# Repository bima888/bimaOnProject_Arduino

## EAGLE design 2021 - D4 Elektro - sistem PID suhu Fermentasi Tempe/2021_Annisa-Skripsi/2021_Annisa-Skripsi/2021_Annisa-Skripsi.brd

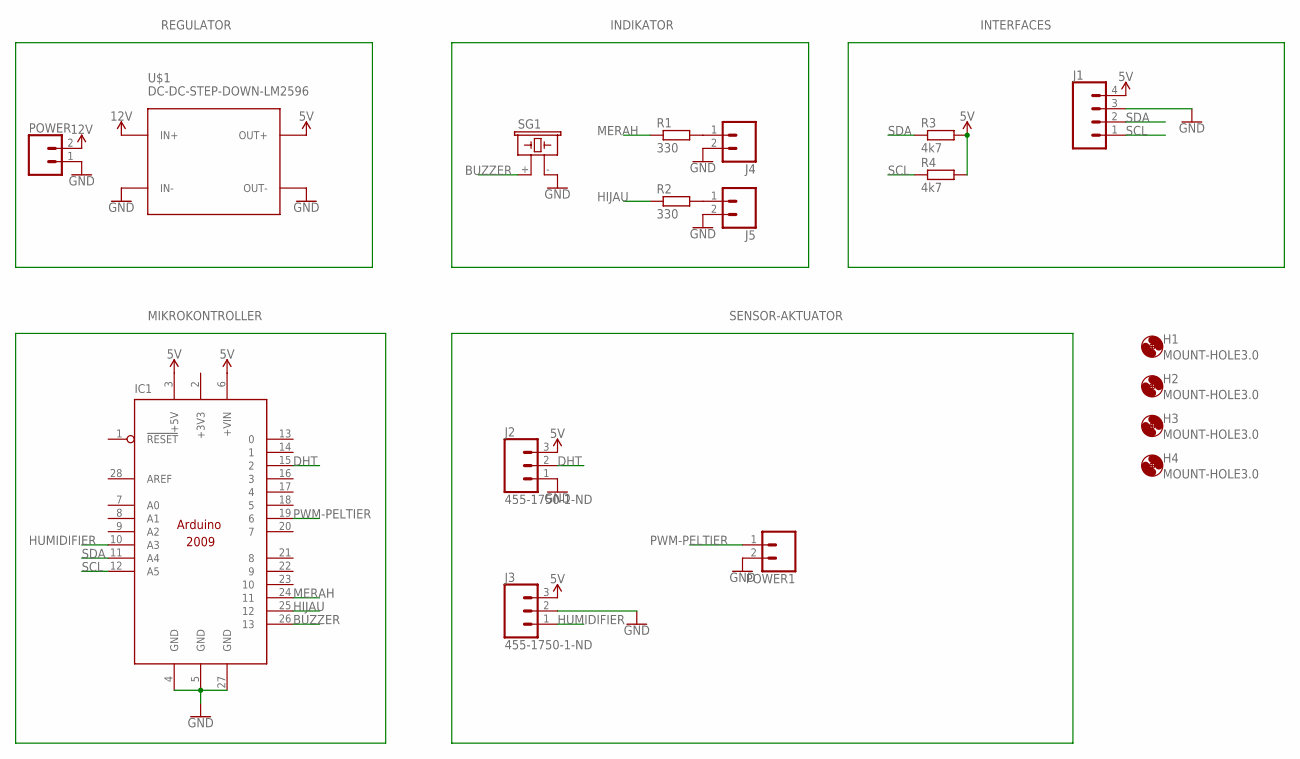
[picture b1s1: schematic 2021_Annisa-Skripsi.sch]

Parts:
H1, H2, H3, H4: MOUNT-HOLE3.0; 3,0
IC1: ARDUINO2009_10; ARDUINO2009
J1: CONN_04PTH; 1X04
J2, J3: 455-1750-1-ND; 1X03
J4, J5: CONN_02; 1X02
POWER, POWER1: CONN_025MM; SCREWTERMINAL-5MM-2
R1, R2: 330; 0207/7
R3, R4: 4k7; 0207/7
SG1: F/CM12P
U$1: DC-DC-STEP-DOWN-LM2596

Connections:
5V: IC1.3 (+5V), IC1.6 (+VIN), J1.4, J2.3, J3.3, R3.2, R4.2, U$1.OUT+
12V: POWER.2, U$1.IN+
+3V3: IC1.2 (+3V3)
BUZZER: IC1.26 (13), SG1.+ (1)
DHT: IC1.15 (2), J2.2
GND: IC1.4 (GND), IC1.5 (GND), IC1.27 (GND), J1.3, J2.1, J3.2, J4.2, J5.2, POWER.1, POWER1.2, SG1.- (2), U$1.IN-, U$1.OUT-
HIJAU: IC1.25 (12), R2.1
HUMIDIFIER: IC1.10 (A3), J3.1
MERAH: IC1.24 (11), R1.1
unnamed: J4.1, R1.2
unnamed: J5.1, R2.2
PWM-PELTIER: IC1.19 (6), POWER1.1
SCL: IC1.12 (A5), J1.1, R4.1
SDA: IC1.11 (A4), J1.2, R3.1

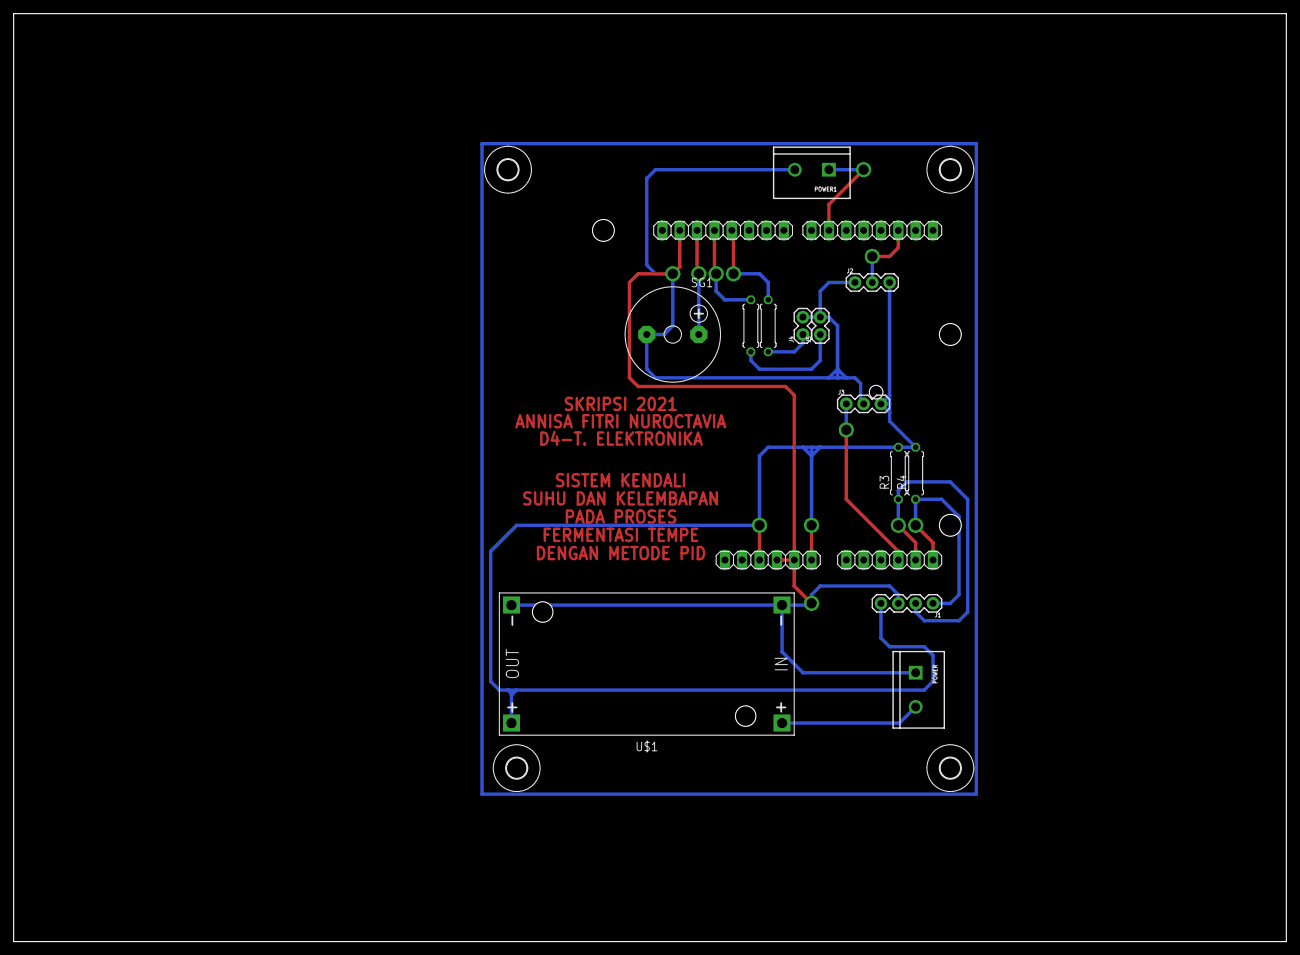
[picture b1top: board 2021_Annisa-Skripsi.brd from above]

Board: 2 copper layers, 186.4 x 135.9 mm, 18 parts (0 on the bottom side), 13 nets.

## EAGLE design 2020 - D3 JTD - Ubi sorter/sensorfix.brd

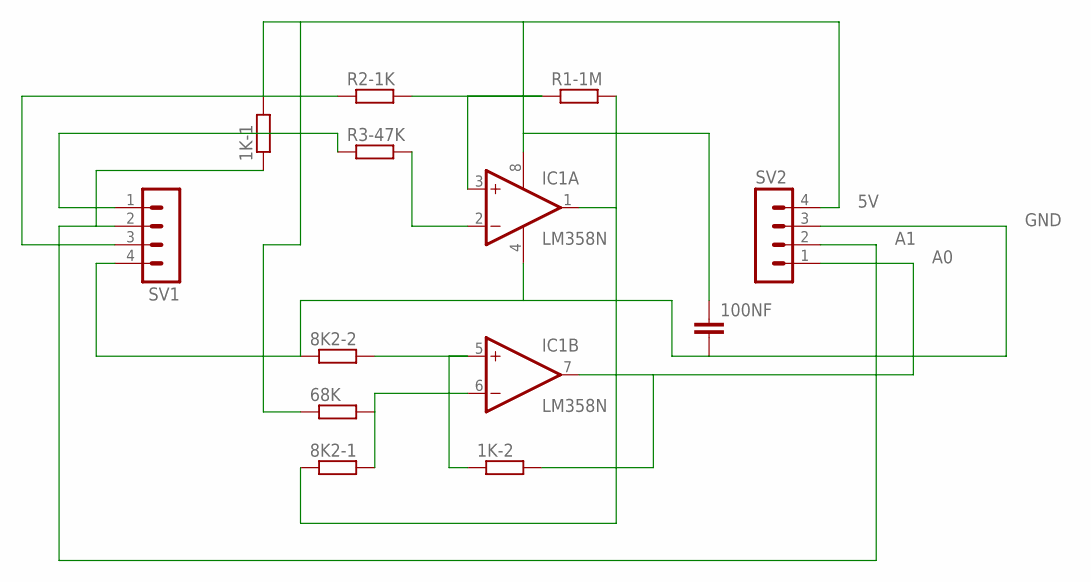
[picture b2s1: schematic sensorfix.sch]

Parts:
1K-1, 1K-2, 8K2-1, 8K2-2, 68K: R-EU_0309/12; 0309/12
100NF: C2.5/6; C2.5-6
IC1: LM358N; DIL08
R1-1M, R2-1K, R3-47K: R-EU_0309/12; 0309/12
SV1, SV2: MA04-1

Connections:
5V: 1K-1.2, 68K.1, 100NF.1, IC1.8 (V+), SV2.4
A0: 1K-2.2, IC1.7 (OUT), SV2.1
A1: 1K-1.1, SV1.2, SV2.2
GND: 8K2-2.1, 100NF.2, IC1.4 (V-), SV1.4, SV2.3
unnamed: IC1.3 (+IN), R1-1M.1, R2-1K.2
unnamed: 8K2-1.1, IC1.1 (OUT), R1-1M.2
unnamed: IC1.2 (-IN), R3-47K.2
unnamed: 1K-2.1, 8K2-2.2, IC1.5 (+IN)
unnamed: 8K2-1.2, 68K.2, IC1.6 (-IN)
unnamed: R3-47K.1, SV1.1
unnamed: R2-1K.1, SV1.3

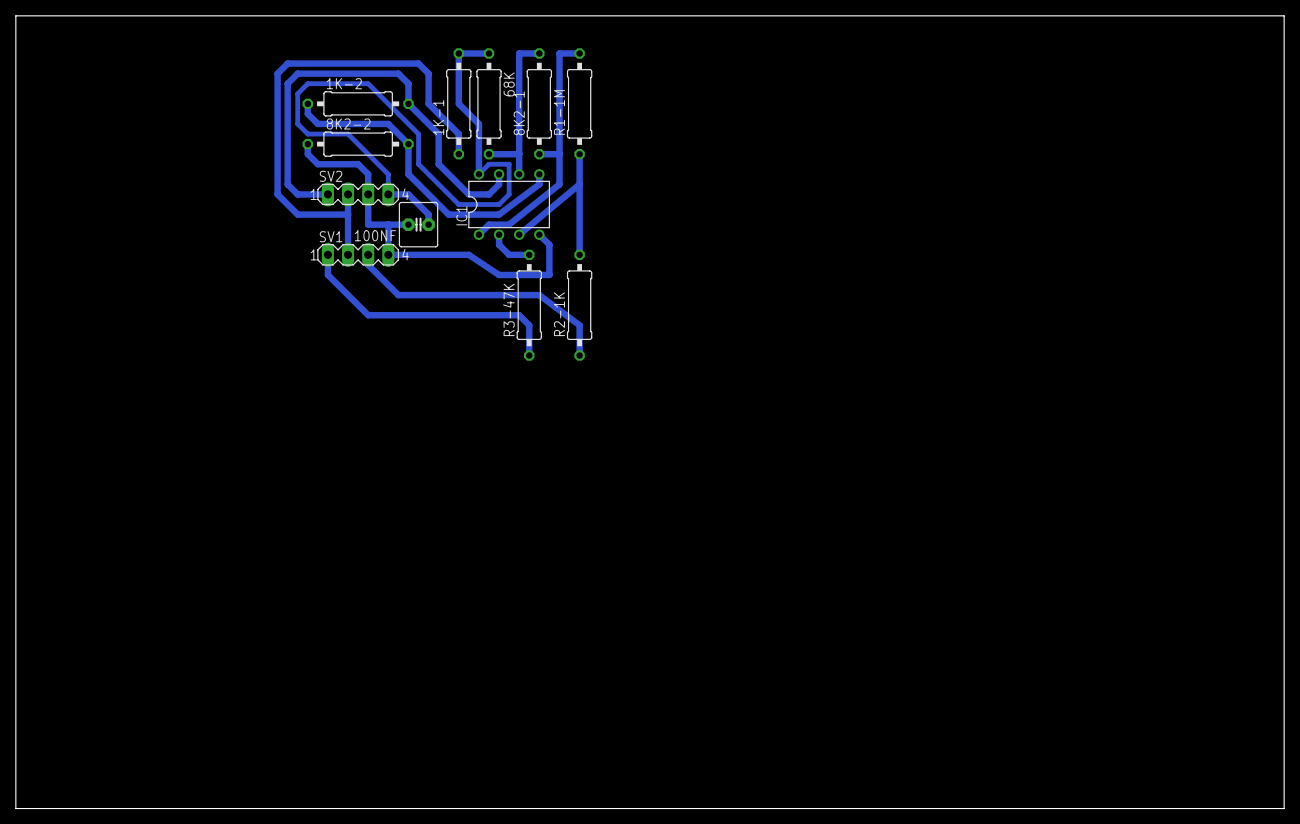
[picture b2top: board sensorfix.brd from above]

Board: 2 copper layers, 160.0 x 100.0 mm, 12 parts (0 on the bottom side), 11 nets.

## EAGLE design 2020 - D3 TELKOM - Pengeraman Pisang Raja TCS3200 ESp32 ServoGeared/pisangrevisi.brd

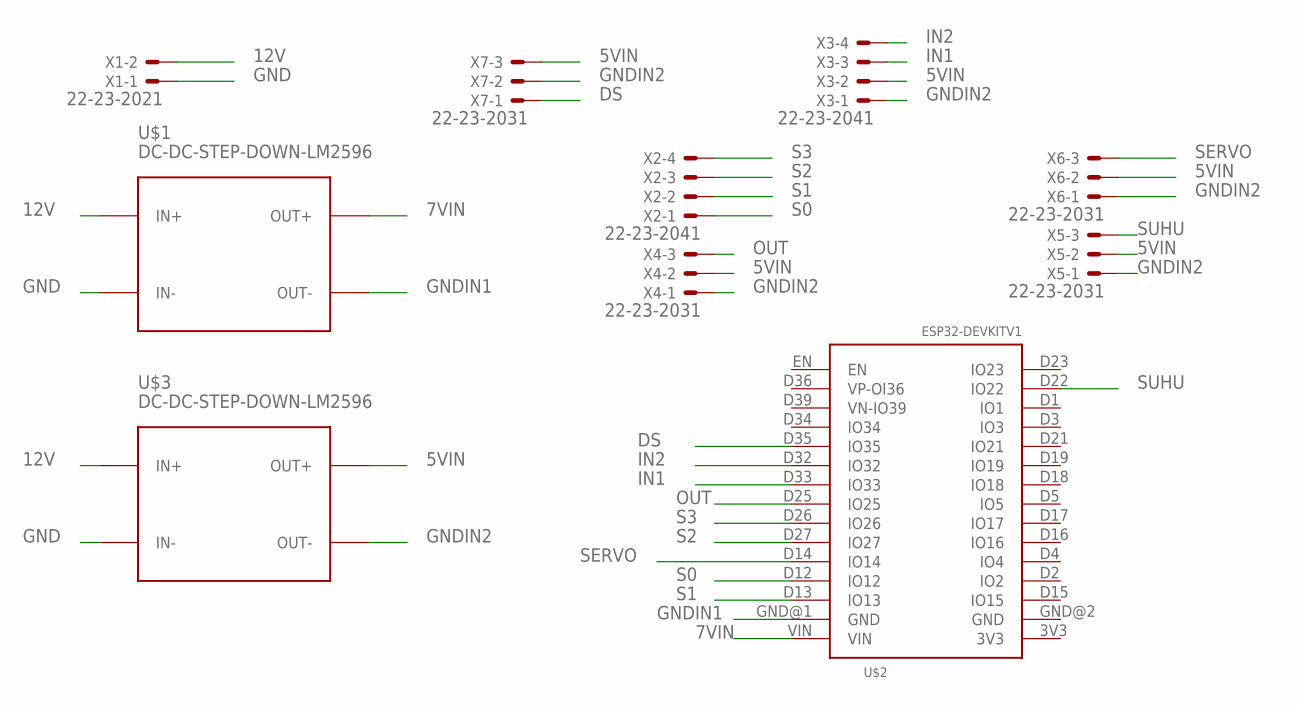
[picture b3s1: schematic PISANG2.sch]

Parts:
U$1, U$3: DC-DC-STEP-DOWN-LM2596
U$2: ESP32DEVKITV1; ESP32-DEVKITV1
X1: 22-23-2021
X2, X3: 22-23-2041
X4, X5, X6, X7: 22-23-2031

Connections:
5VIN: U$3.OUT+, X3.2, X4.2, X5.2, X6.2, X7.3
7VIN: U$1.OUT+, U$2.VIN
12V: U$1.IN+, U$3.IN+, X1.2
DS: U$2.D35 (IO35), X7.1
GND: U$1.IN-, U$3.IN-, X1.1
GNDIN1: U$1.OUT-, U$2.GND@1 (GND)
GNDIN2: U$3.OUT-, X3.1, X4.1, X5.1, X6.1, X7.2
IN1: U$2.D33 (IO33), X3.3
IN2: U$2.D32 (IO32), X3.4
OUT: U$2.D25 (IO25), X4.3
S0: U$2.D12 (IO12), X2.1
S1: U$2.D13 (IO13), X2.2
S2: U$2.D27 (IO27), X2.3
S3: U$2.D26 (IO26), X2.4
SERVO: U$2.D14 (IO14), X6.3
SUHU: U$2.D22 (IO22), X5.3

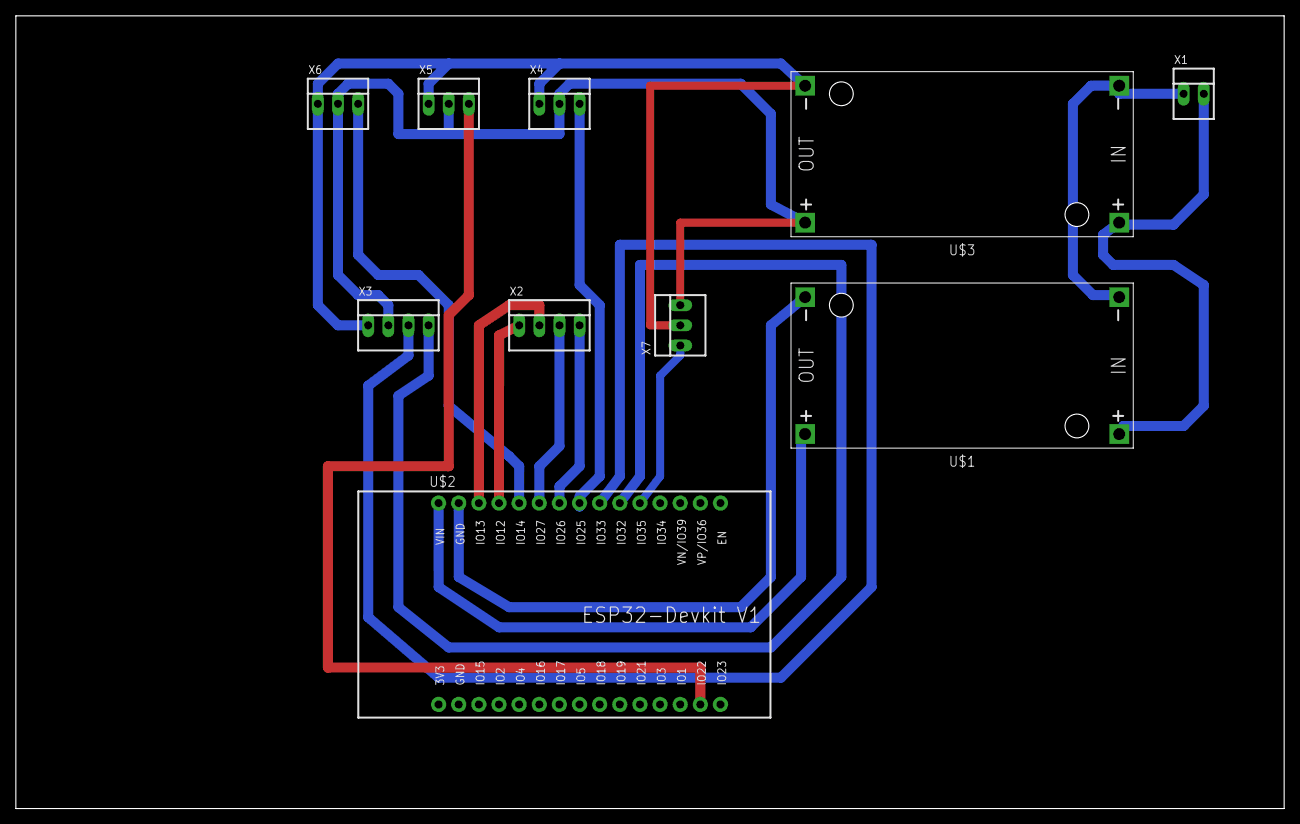
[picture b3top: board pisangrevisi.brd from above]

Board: 2 copper layers, 160.0 x 100.0 mm, 10 parts (0 on the bottom side), 16 nets.

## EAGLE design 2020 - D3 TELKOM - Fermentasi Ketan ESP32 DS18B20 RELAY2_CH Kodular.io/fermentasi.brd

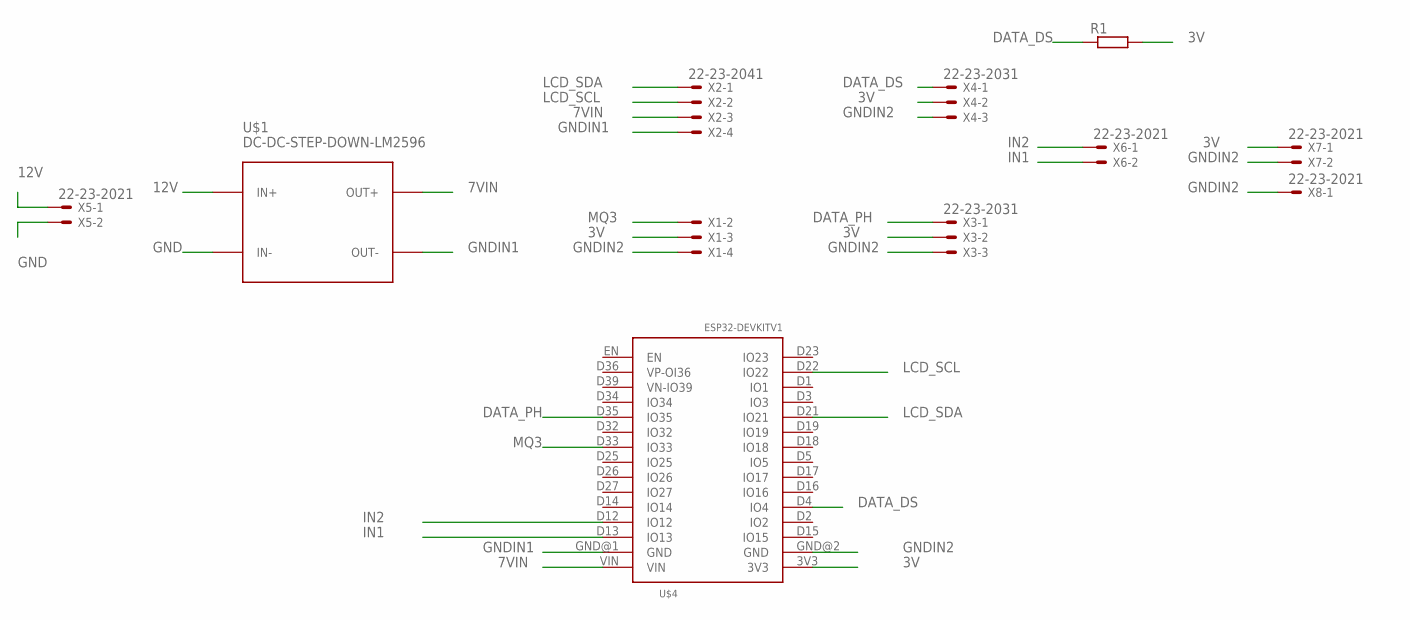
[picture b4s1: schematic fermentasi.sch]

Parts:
R1: R-EU_0207/10; 0207/10
U$1: DC-DC-STEP-DOWN-LM2596
U$4: ESP32DEVKITV1; ESP32-DEVKITV1
X1, X2: 22-23-2041
X3, X4: 22-23-2031
X5, X6, X7, X8: 22-23-2021

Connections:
3V: R1.2, U$4.3V3, X1.3, X3.2, X4.2, X7.1
7VIN: U$1.OUT+, U$4.VIN, X2.3
12V: U$1.IN+, X5.1
DATA_DS: R1.1, U$4.D4 (IO4), X4.1
DATA_PH: U$4.D35 (IO35), X3.1
GND: U$1.IN-, X5.2
GNDIN1: U$1.OUT-, U$4.GND@1 (GND), X2.4
GNDIN2: U$4.GND@2 (GND), X1.4, X3.3, X4.3, X7.2, X8.1
IN1: U$4.D13 (IO13), X6.2
IN2: U$4.D12 (IO12), X6.1
LCD_SCL: U$4.D22 (IO22), X2.2
LCD_SDA: U$4.D21 (IO21), X2.1
MQ3: U$4.D33 (IO33), X1.2

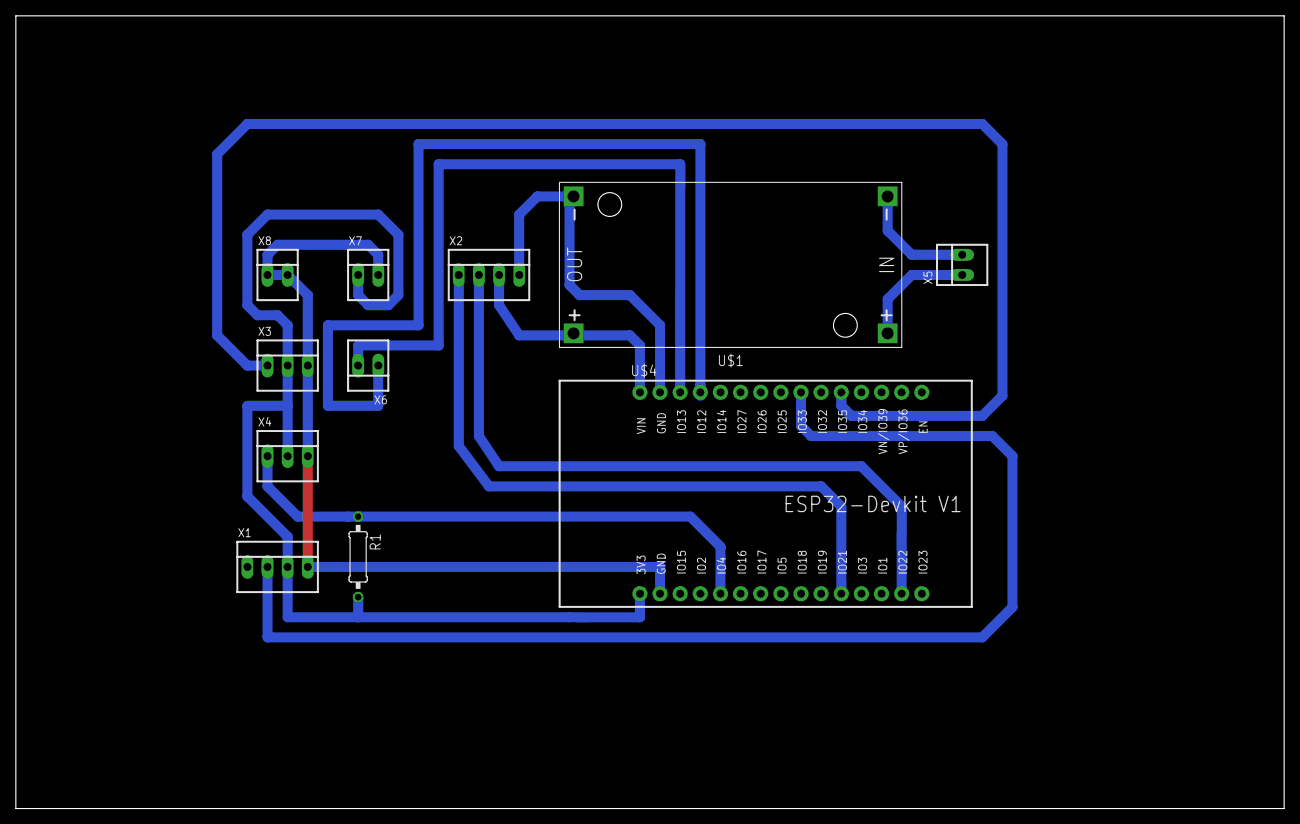
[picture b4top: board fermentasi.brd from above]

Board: 2 copper layers, 160.0 x 100.0 mm, 11 parts (0 on the bottom side), 13 nets.

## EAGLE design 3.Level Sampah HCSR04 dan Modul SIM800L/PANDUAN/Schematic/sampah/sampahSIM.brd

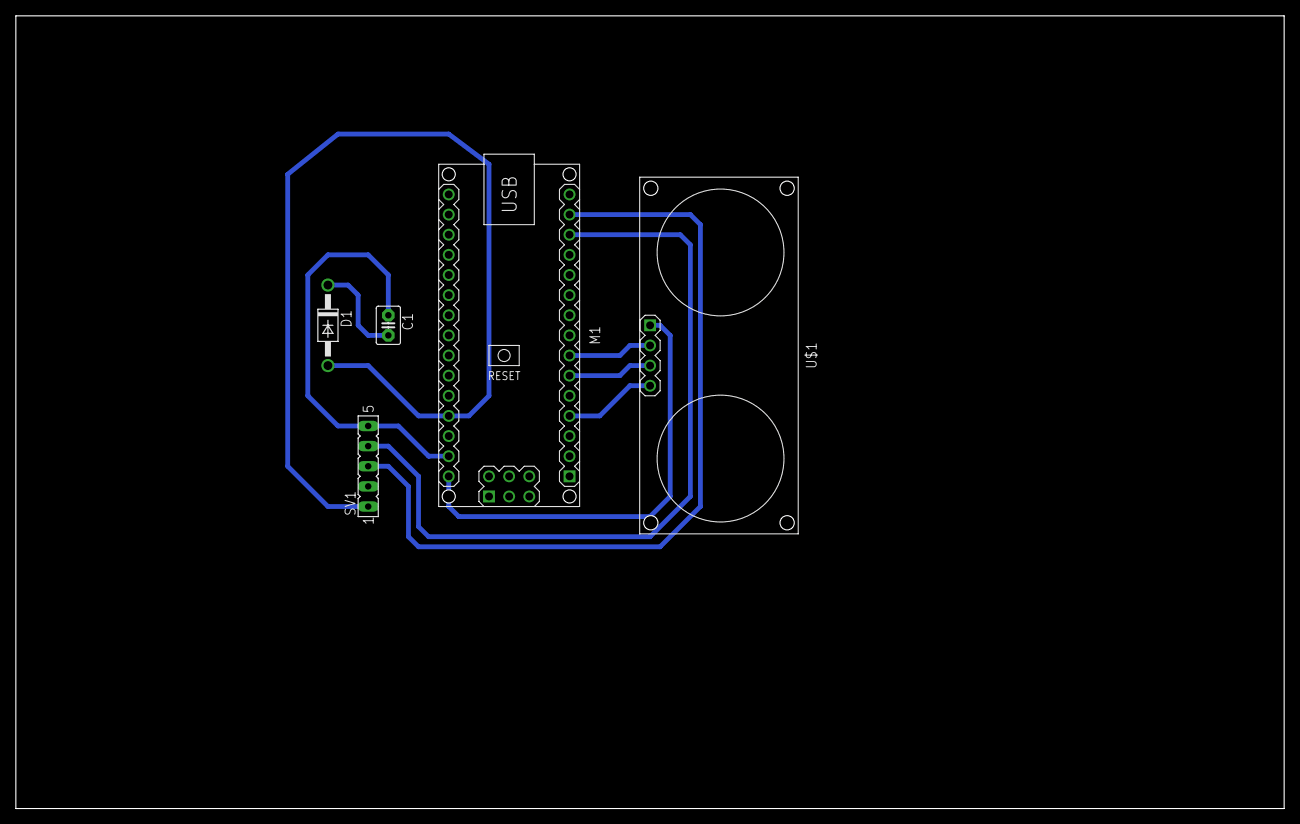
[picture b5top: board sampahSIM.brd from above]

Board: 2 copper layers, 160.0 x 100.0 mm, 5 parts (0 on the bottom side), 9 nets.

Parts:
C1: C2.5-3
D1: 1N4004; DO41-10
M1: ARDUINO-NANO-3.0#ISP
SV1: FE05-1
U$1: ULTRASONIC-HC-SR04

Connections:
unnamed: C1.2, D1.C
unnamed: C1.1, M1.J2.2, SV1.5
unnamed: M1.J1.13, SV1.4
unnamed: M1.J1.14, SV1.3
unnamed: D1.A, M1.J2.4, SV1.1
unnamed: M1.J2.1, U$1.1
unnamed: M1.J1.7, U$1.2
unnamed: M1.J1.6, U$1.3
unnamed: M1.J1.4, U$1.4

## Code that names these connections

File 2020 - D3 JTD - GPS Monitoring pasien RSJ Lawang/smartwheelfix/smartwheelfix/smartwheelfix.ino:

#include <ArduinoJson.h>
#include <WiFi.h>
#include <IOXhop_FirebaseESP32.h>

#define FIREBASE_HOST "wheel-c097a.firebaseio.com"              //Your Firebase Project URL goes here without "http:" , "\" and "/"
#define FIREBASE_AUTH "WwFRAezGKnlE4gs8WYuL4p65RdNAMP2M1HypuPDC"       //Your Firebase Database Secret goes here
#define WIFI_SSID "diki"                                     //your WiFi SSID for which yout NodeMCU connects
#define WIFI_PASSWORD "misquinn"                                      //Password of your wifi network 

#include <TinyGPS++.h>
TinyGPSPlus gps;

int R ; // variabel untuk seleksi kondisi relay
int metode ; // untuk switch case
float latitude ;
float longitude ;
String lati, longi ; //variabel untuk di kirim ke firebase

#define relay 4
#define buzzer 5
#define ijo 23
#define merah 22
#define putih 21

void setup() {
  Serial.begin(9600) ;
  pinMode(ijo,OUTPUT) ; //Led Hijau Indikator Kursi Roda Jalan/nyala// Relay OFF
  pinMode(merah,OUTPUT) ; //Led Merah Indikator Kursi Roda Mati/waktu habis// Relay ON
  pinMode(buzzer,OUTPUT) ;  //Buzzer nyala indikator kursi mau habis // Relay ON
  pinMode(putih,OUTPUT) ; //Led Putih nyala indikator Standby// Relay OFF
  pinMode(relay,OUTPUT) ; //pin Relay
  WiFi.begin(WIFI_SSID,WIFI_PASSWORD);
  Serial.print("connecting");
  while (WiFi.status()!=WL_CONNECTED){
    Serial.print(".");
    delay(500);
  }
  Serial.println();
  Serial.print("connected:");
  Serial.println(WiFi.localIP());
  Firebase.begin(FIREBASE_HOST,FIREBASE_AUTH);
}

void loop() {
    while (Serial.available() > 0){
    gps.encode(Serial.read());
    if (gps.location.isUpdated()){
      latitude =  gps.location.lat() ; //mendapatkan nilai latitude
      longitude = gps.location.lng() ; //mendapatkan nilai longitude
      lati = String(latitude,6) ;
      longi = String (longitude,6) ;
      Serial.print("Latitude= "); 
      Serial.print (latitude,6); //Serial.print(gps.location.lat(), 6);
      Serial.print(" Longitude= "); 
      Serial.println (longitude,6); //Serial.println(gps.location.lng(), 6);
      Firebase.setString("latitude",lati);
      Firebase.setString("longitude",longi);
      
   R=Firebase.getString("durasi").toInt();   //Pembacaan di Firebase
   Serial.print(R) ;
   if(R==0)
   metode = 1 ;
   else if(R==1 || R==2 || R==3)
   metode = 2 ;
   else if (R==5)
   metode = 3 ;
   else if (R==9)
   metode = 4 ;
switch (metode){
  case 1 : mati() ;
  break ;
  case 2 : nyala() ;
  break ;
  case 3 : standby() ;
  break ;
  case 4 : buzer() ;
  break ;
}
    }
    }
     R=Firebase.getString("durasi").toInt();   //Pembacaan di Firebase
     Serial.print(R) ;
     if(R==0)
     metode = 1 ;
     else if(R==1 || R==2 || R==3)
     metode = 2 ;
     else if (R==5)
     metode = 3 ;
     else if (R==9)
     metode = 4 ;
     
switch (metode){
  case 1 : mati() ;
  break ;
  case 2 : nyala() ;
  break ;
  case 3 : standby() ;
  break ;
  case 4 : buzer() ;
  break ;
}
}
void mati(){
  Serial.println(" Kursi Roda Ngunci") ; //Relay ON led merah nyala
  digitalWrite(ijo,LOW) ;
  digitalWrite(putih,LOW) ;
  digitalWrite(buzzer,LOW);
  digitalWrite(merah,HIGH) ;
  digitalWrite(relay,HIGH); //lampu di relay mati
}
void nyala() {
  Serial.println(" Kursi Roda Aktif Bisa Jalan") ; // Relay OFF led hijau nyala
  digitalWrite(ijo,HIGH) ;
  digitalWrite(merah,LOW) ;
  digitalWrite(buzzer,LOW) ;
  digitalWrite(putih,LOW) ;
  digitalWrite(relay,LOW); //lampu di relay nyala
}
void standby() { 
  Serial.println(" Kursi Roda Standby") ; //Relay OFF led putih nyala
  digitalWrite(putih,HIGH) ;
  digitalWrite(merah,LOW) ;
  digitalWrite(buzzer,LOW) ;
  digitalWrite(ijo,LOW) ;
  digitalWrite(relay,LOW); //lampu di relay nyala
}
void buzer(){
  Serial.println(" Kursi Roda Mau Habis") ; //Relay OFF led hijau nyala
  digitalWrite(ijo,HIGH) ;
  digitalWrite(buzzer,HIGH);
  digitalWrite(relay,LOW);
  delay(200) ;
  digitalWrite(ijo,HIGH) ;
  digitalWrite(buzzer,LOW);
  digitalWrite(relay,LOW);
  delay(200) ;
}

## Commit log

2021-05-13 Create HeatExchanger
2021-05-13 Create date
2021-05-13 Create MultiStation

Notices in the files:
parts and their libraries:
diy-modules: Released under the Creative Commons Attribution 4.0 International License: http://creativecommons.org/licenses/by/4.0
SparkFun-Connectors: Licensing: Creative Commons ShareAlike 4.0 International - https://creativecommons.org/licenses/by-sa/4.0
